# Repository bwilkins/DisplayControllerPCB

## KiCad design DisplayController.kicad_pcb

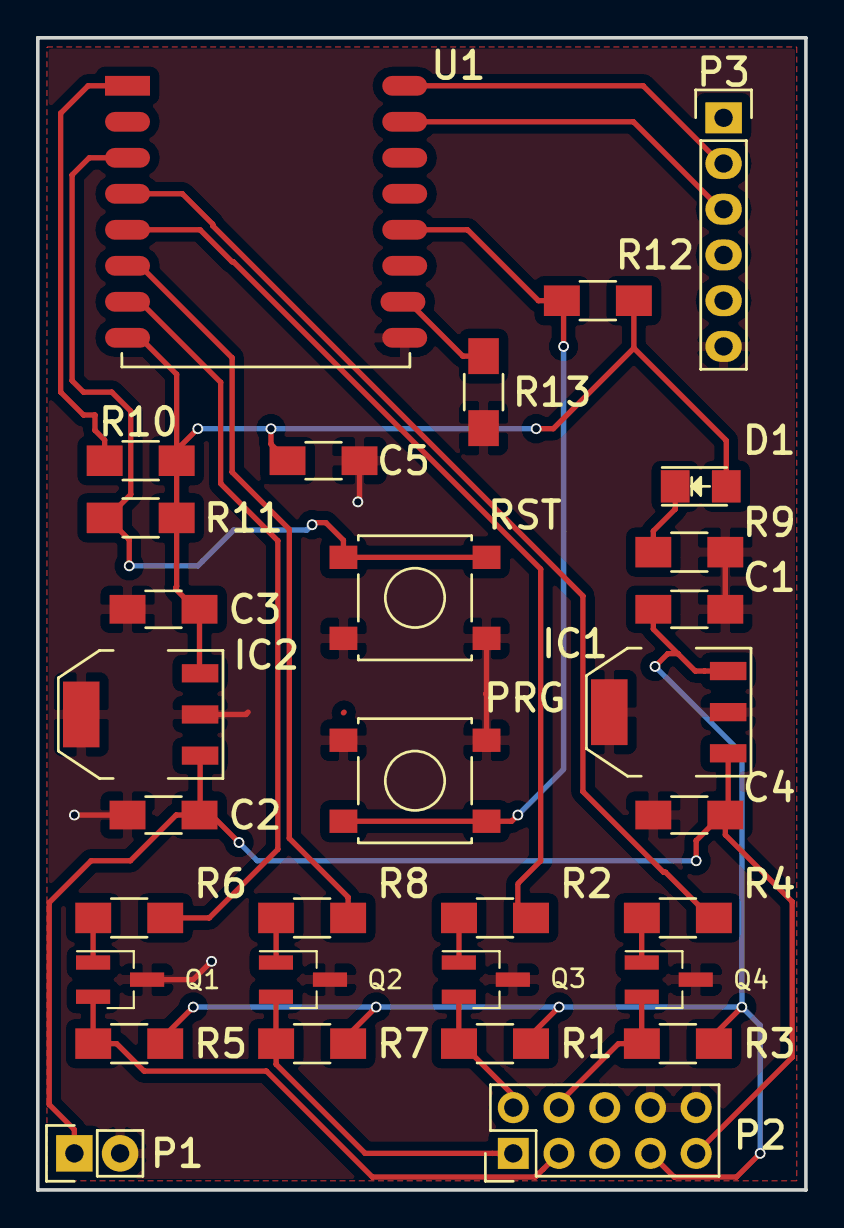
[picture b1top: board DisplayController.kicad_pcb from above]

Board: 2 copper layers, 42.7 x 64.0 mm, 31 parts (0 on the bottom side), 23 nets.

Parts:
C1, C3, C5: 10uF; C_1206_HandSoldering
C2, C4: 100nF; C_1206_HandSoldering
D1: LED; LED_1206
IC1: LM2937IMP-5.0; SOT-223
IC2: LM2937IMP-3.3; SOT-223
P1: PWR; Pin_Header_Straight_1x02
P2: OUTPUT; Pin_Header_Straight_2x05
P3: Programming Header; Pin_Header_Straight_1x06
Q1, Q2, Q3, Q4: SMBT2222A; SOT-23_Handsoldering
R1, R2, R3, R4, R5, R6, R7, R8, R10, R11, R12, R13: 10K; R_1206_HandSoldering
R9: 60R; R_1206_HandSoldering
SW1: RST; SW_SPST_B3S-1000
SW2: PRG; SW_SPST_B3S-1000
U1: ESP-12; ESP-12-SMD

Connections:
+3V3: C3.1, C5.1, D1.2, IC2.3, R10.2, R11.2, R12.1, U1.8
+5V: C1.1, IC1.3, P2.7, R1.2, R3.2, R5.2, R7.2
+9V: C2.1, C4.1, IC1.1, IC2.1, P1.1, P2.9
GND: C1.2, C2.2, C3.2, C4.2, C5.2, IC1.2, IC1.4, IC2.2, IC2.4, P1.2, P2.8, P2.10, P3.6, Q1.3, Q2.3, Q3.3, Q4.3, R9.1, R13.1, SW1.2, SW2.1, U1.9
unnamed: D1.1, R9.2
unnamed: P2.1, Q2.2, R7.1
unnamed: P2.2, Q3.2, R1.1
unnamed: P2.3, Q1.2, R5.1
unnamed: P2.4, Q4.2, R3.1
unnamed: P3.2, U1.16
unnamed: P3.3, U1.15
unnamed: Q1.1, R6.1
unnamed: Q2.1, R8.1
unnamed: Q3.1, R2.1
unnamed: Q4.1, R4.1
unnamed: R2.2, U1.5
unnamed: R4.2, U1.4
unnamed: R6.2, U1.7
unnamed: R8.2, U1.6
unnamed: R10.1, U1.1
unnamed: R11.1, SW1.1, U1.3
unnamed: R12.2, SW2.2, U1.12
unnamed: R13.2, U1.10

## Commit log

2016-12-04 Initial Commit - first draft of version 2 (version 1 was designed in eagle)
2016-12-05 For safe keeping.
2016-12-05 Adding a logo and GND plane on both sides
2016-12-10 WIP: converted ESP footprint to SMD (pads). Now rerouting and changing configuration of signal pins so that signal routing is easier.
2016-12-10 rev2, About to create Gerbers
2016-12-10 Board should be ready to go
2016-12-10 Adding "final" gerbers
2016-12-12 Changing SOT-223 footprint to SOT-23-3. Respin and resize of the board.
2016-12-12 Adding a gitignore file for the DS_Store crap
2017-01-21 Keeping everything up-to-date since last push was last year!
